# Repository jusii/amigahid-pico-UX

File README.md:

# amigahid-pico

> **Old, moved:** this project is now **Ninepin UX** at [github.com/jusii/ninepin-ux](https://github.com/jusii/ninepin-ux) (boards, firmware, case, full history). This fork stays only for upstream-facing work on [borb/amigahid-pico](https://github.com/borb/amigahid-pico).

**about this fork:** this fork adds support for attaching a *real amiga keyboard* to controller port 2 (build with `-DPORT2_ROLE=KEYBOARD`; see [installation](./doc/installation.md) and [hardware](./doc/hardware.md)). it is based on upstream [pr #44](https://github.com/borb/amigahid-pico/pull/44) (bluetooth support by stefan reinauer) — see that pr for details of the bluetooth work. tested configuration: rev 5 pcb, standard pico (non-w), `BOARD_HIDPICO_REV4` firmware target with `PORT2_ROLE=KEYBOARD`. the original project lives at [borb/amigahid-pico](https://github.com/borb/amigahid-pico).

## introduction

amigahid-pico uses the rp2040 microcontroller (e.g. the raspberry pi pico) in a carrier board to attach usb input devices to a standard amiga without the need for a usb stack on the amiga itself.

it currently supports keyboards and mice and provides connection via the internal keyboard connector, the rj11/din socket on big-box amigas, and via the controller ports.

**this project is very much a work in progress.**

## **important note**

* current kicad files are for the r5 pcb, which is mostly identical to r4. there is no separate r5 firmware target: build `BOARD_HIDPICO_REV4` (the default) — this fork has been built and tested on an r5 board with the rev 4 target. controller port 2 can now be used as an input for a real amiga keyboard via `-DPORT2_ROLE=KEYBOARD` (see the [hardware](./doc/hardware.md) guide for wiring).

* **always read the [errata](./doc/errata.md) section for the current pcb layout before deciding whether or not to build.**

## documentation

* [installation](./doc/installation.md)
* [hardware](./doc/hardware.md)
* [errors in revisions (errata)](./doc/errata.md)

## history

this project is a rewrite of the [amigahid](https://github.com/borb/amigahid) project to the rp2040 microcontroller.

originally, after the retirement of the arduino adk board and shortening availability of the max3421e "usb host shield" for arduino boards, the need for a cheap, easy and continually available replacement was sought.

at first, the uhs mini via a level shifter seemed ideal, but significant issues were found convincing it to work with a variety of arduino boards.

the rp2040 made sense as a target because it is widely available, has sufficient physical connections and is powerful enough to meet multiple needs.

## what is the latency of this?

i have not measured the latency, but the keyboard signals are sent out the moment they are received on the usb bus. the potential latency is likely fractionally longer than the amiga mcu but bear in mind the rp2040 is significantly faster than the standard amiga keyboard controller.

## roadmap

please see the issues tab on the [github repository](https://github.com/borb/amigahid-pico) for the current list of planned features. the tl;dr is:

normal:
* i<sup>2</sup>c display for config/status
* controller emulation
    * keyboard-based controller emulation (use udlr for directions?)
* flash memory-based configuration
* possible amiga-side control panel (using bidirectional controller port signals)
* rotary control simulation (for controlling gotek drives)

crazy talk:
* non-amiga support
* non-hidbp support
* analogue/paddle emulation
* fix some tinyusb issues (hotplug, timing-related instability)

## license

on the fence at the moment, but the current license choice is Eclipse Public License 2.0 (EPL-2.0).

## third party licenses

* µgui: this code contains 'µgui' by achim döbler; the license for this can be read at in the [display readme](./src/display/README.md)

## whuh... who?

nine <[nine@aphlor.org](mailto:nine@aphlor.org)>

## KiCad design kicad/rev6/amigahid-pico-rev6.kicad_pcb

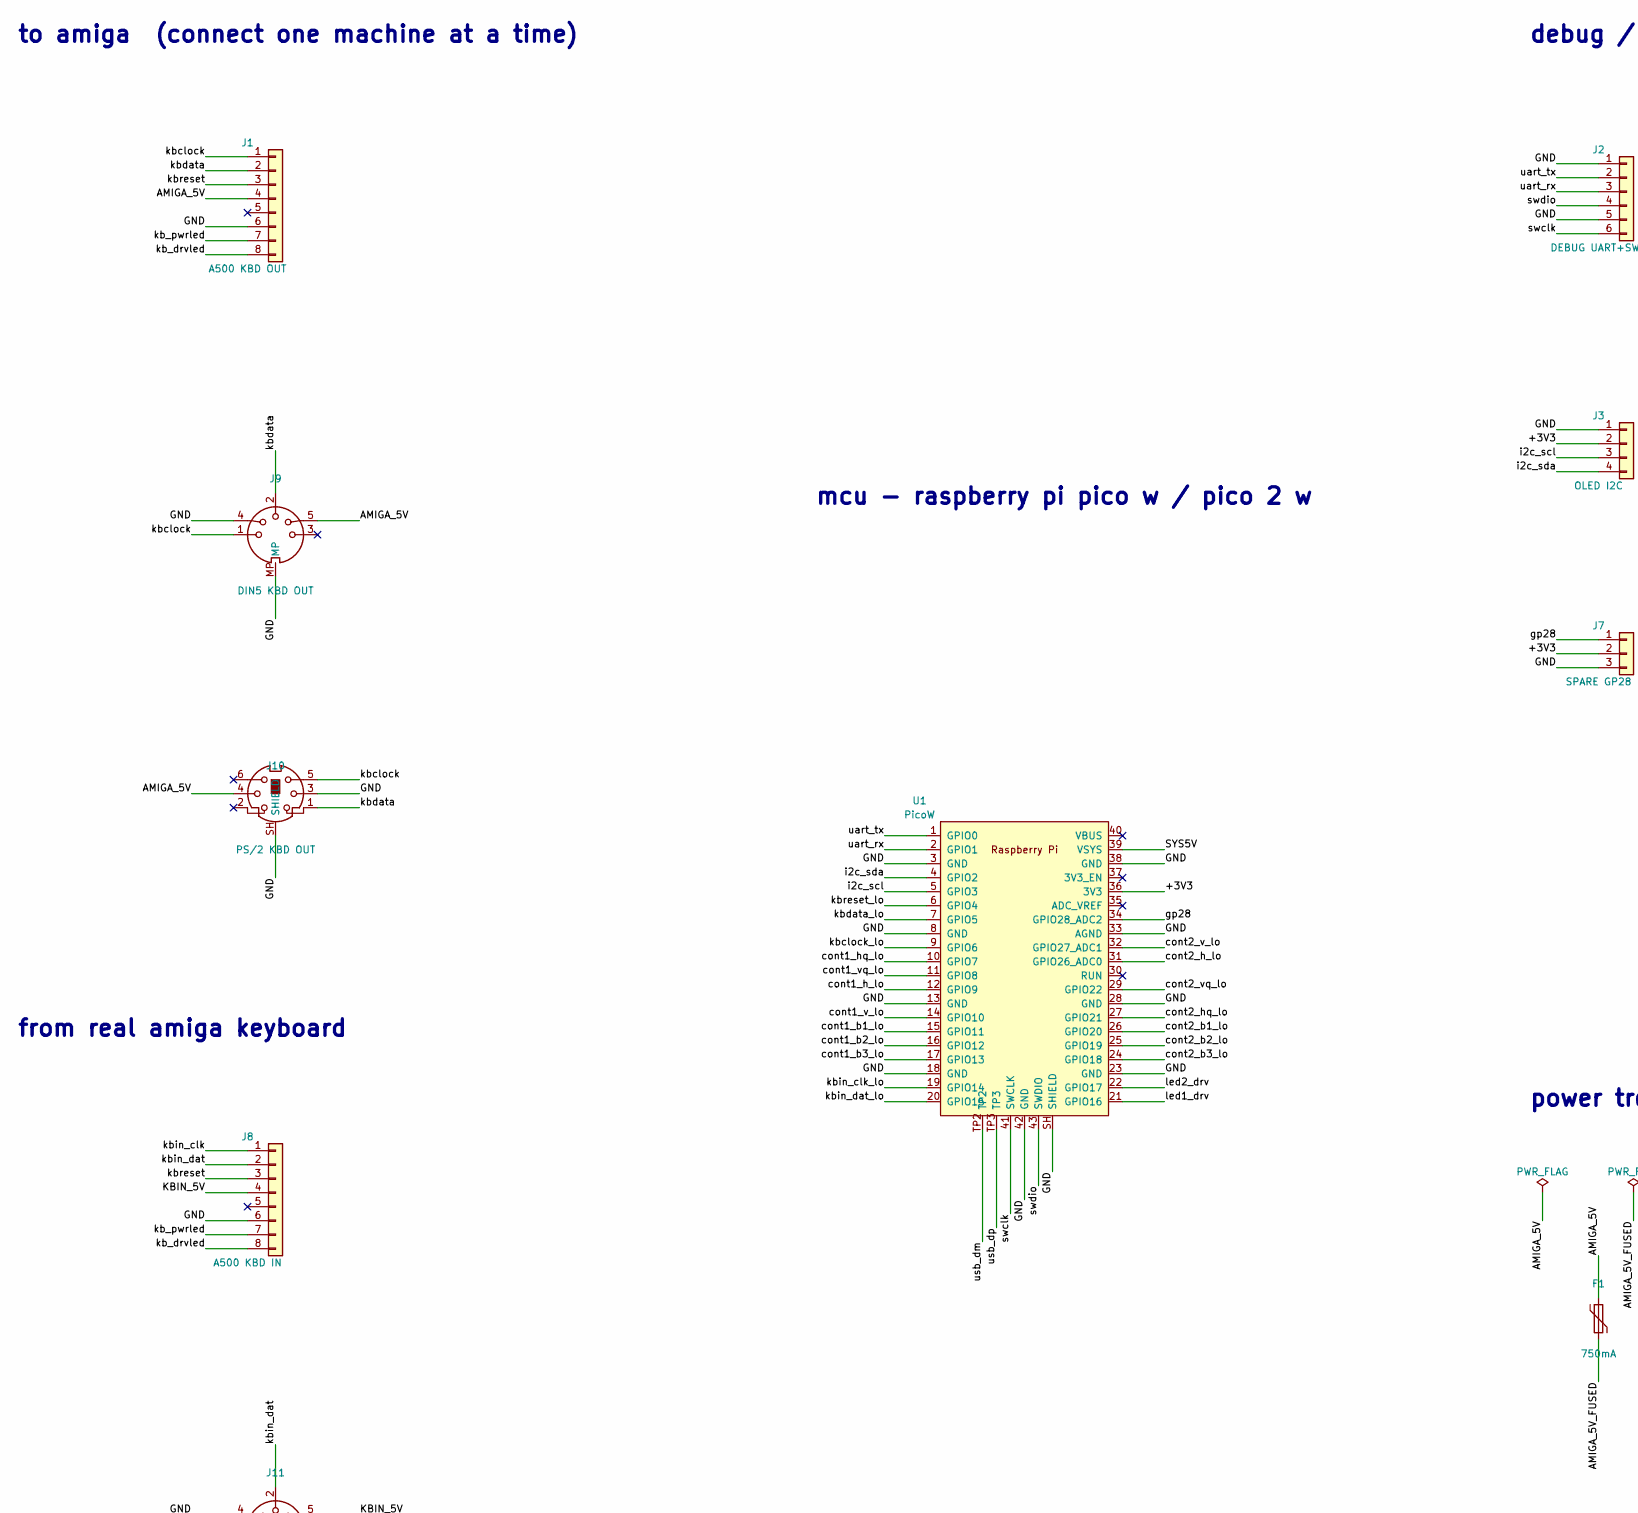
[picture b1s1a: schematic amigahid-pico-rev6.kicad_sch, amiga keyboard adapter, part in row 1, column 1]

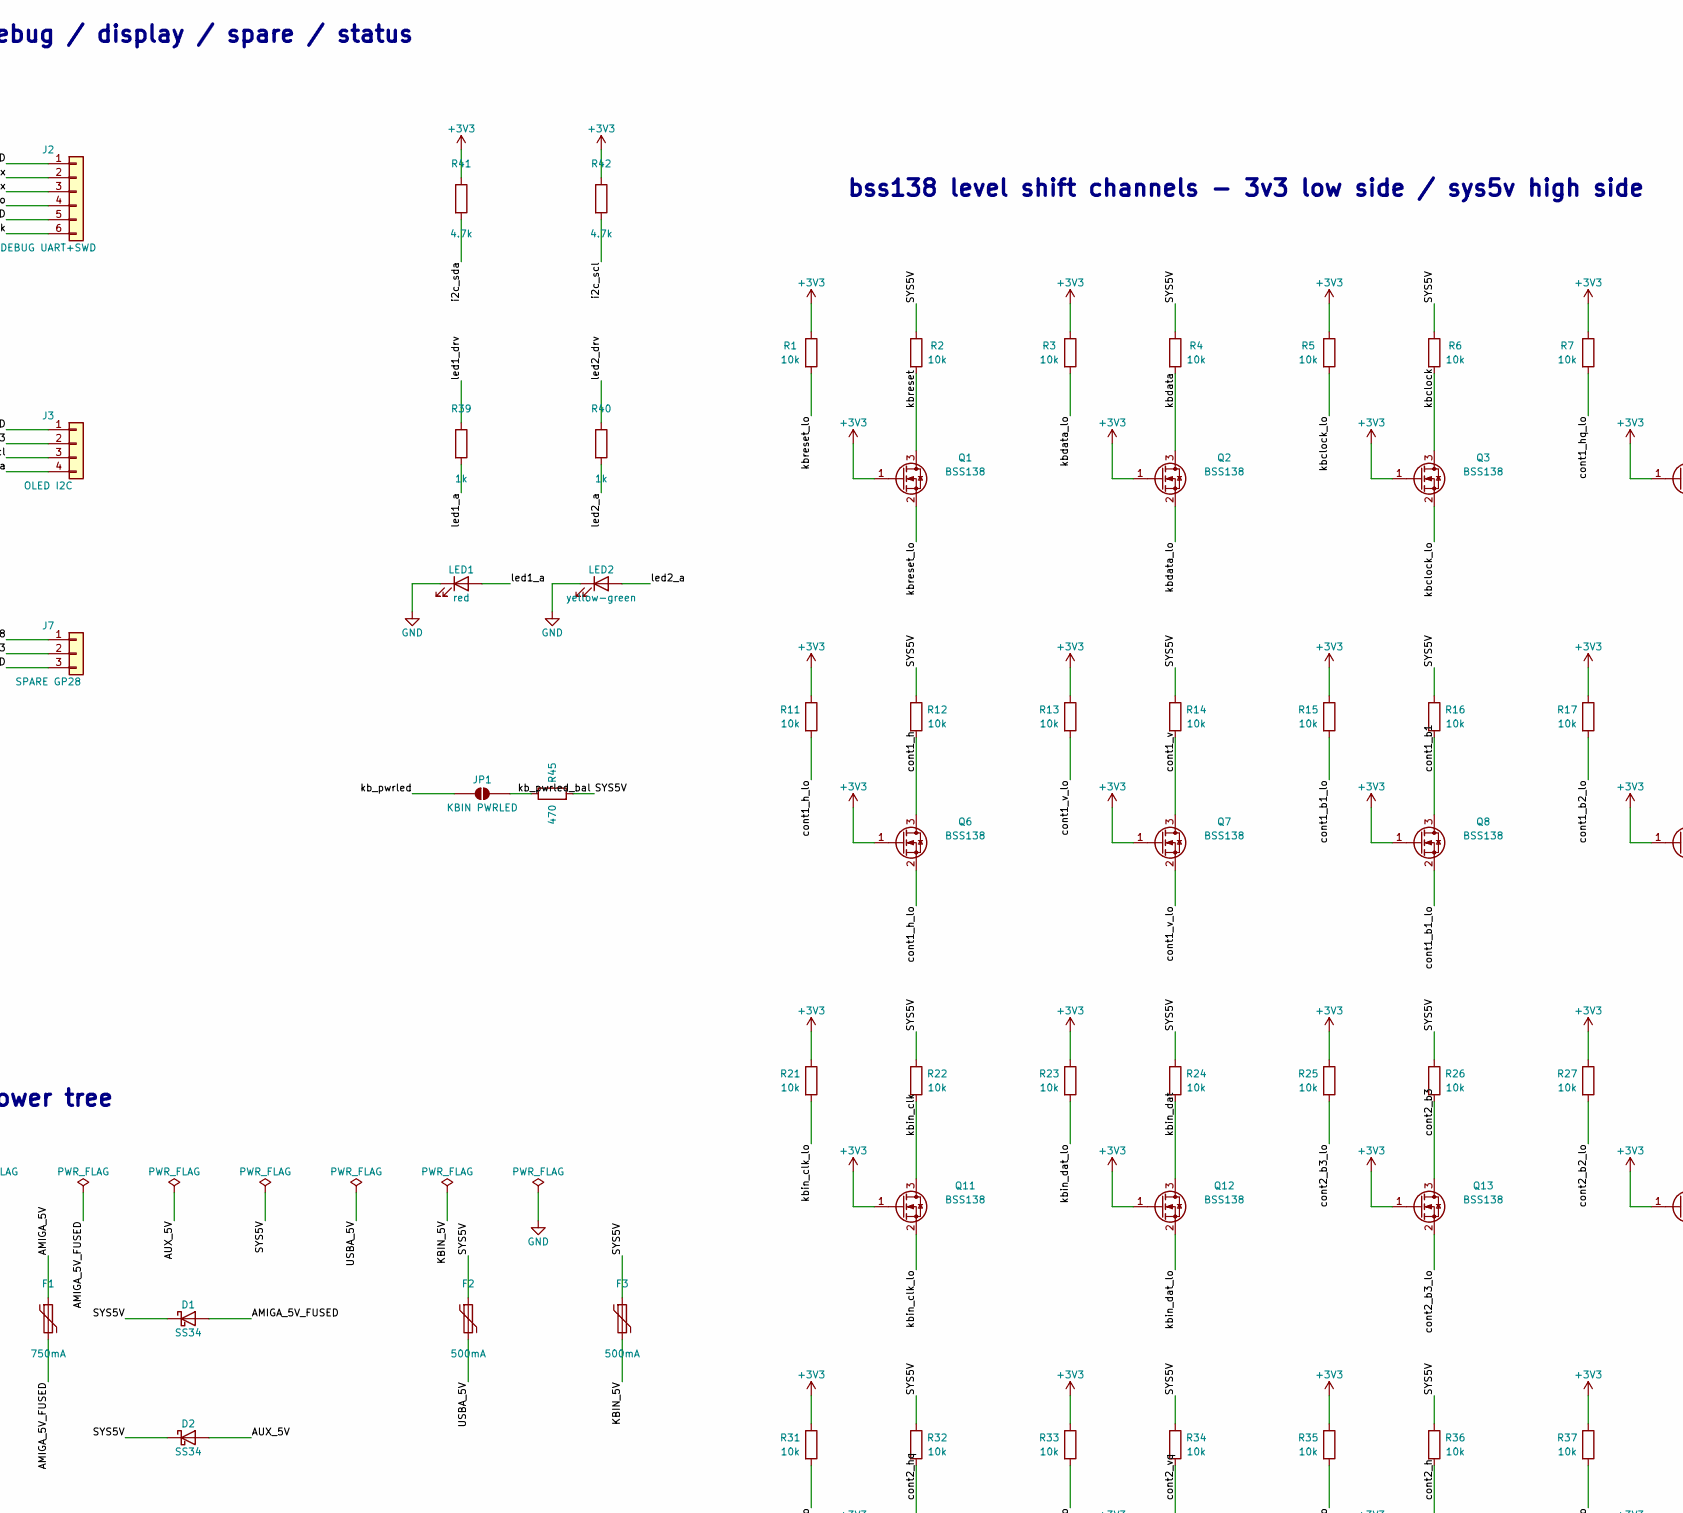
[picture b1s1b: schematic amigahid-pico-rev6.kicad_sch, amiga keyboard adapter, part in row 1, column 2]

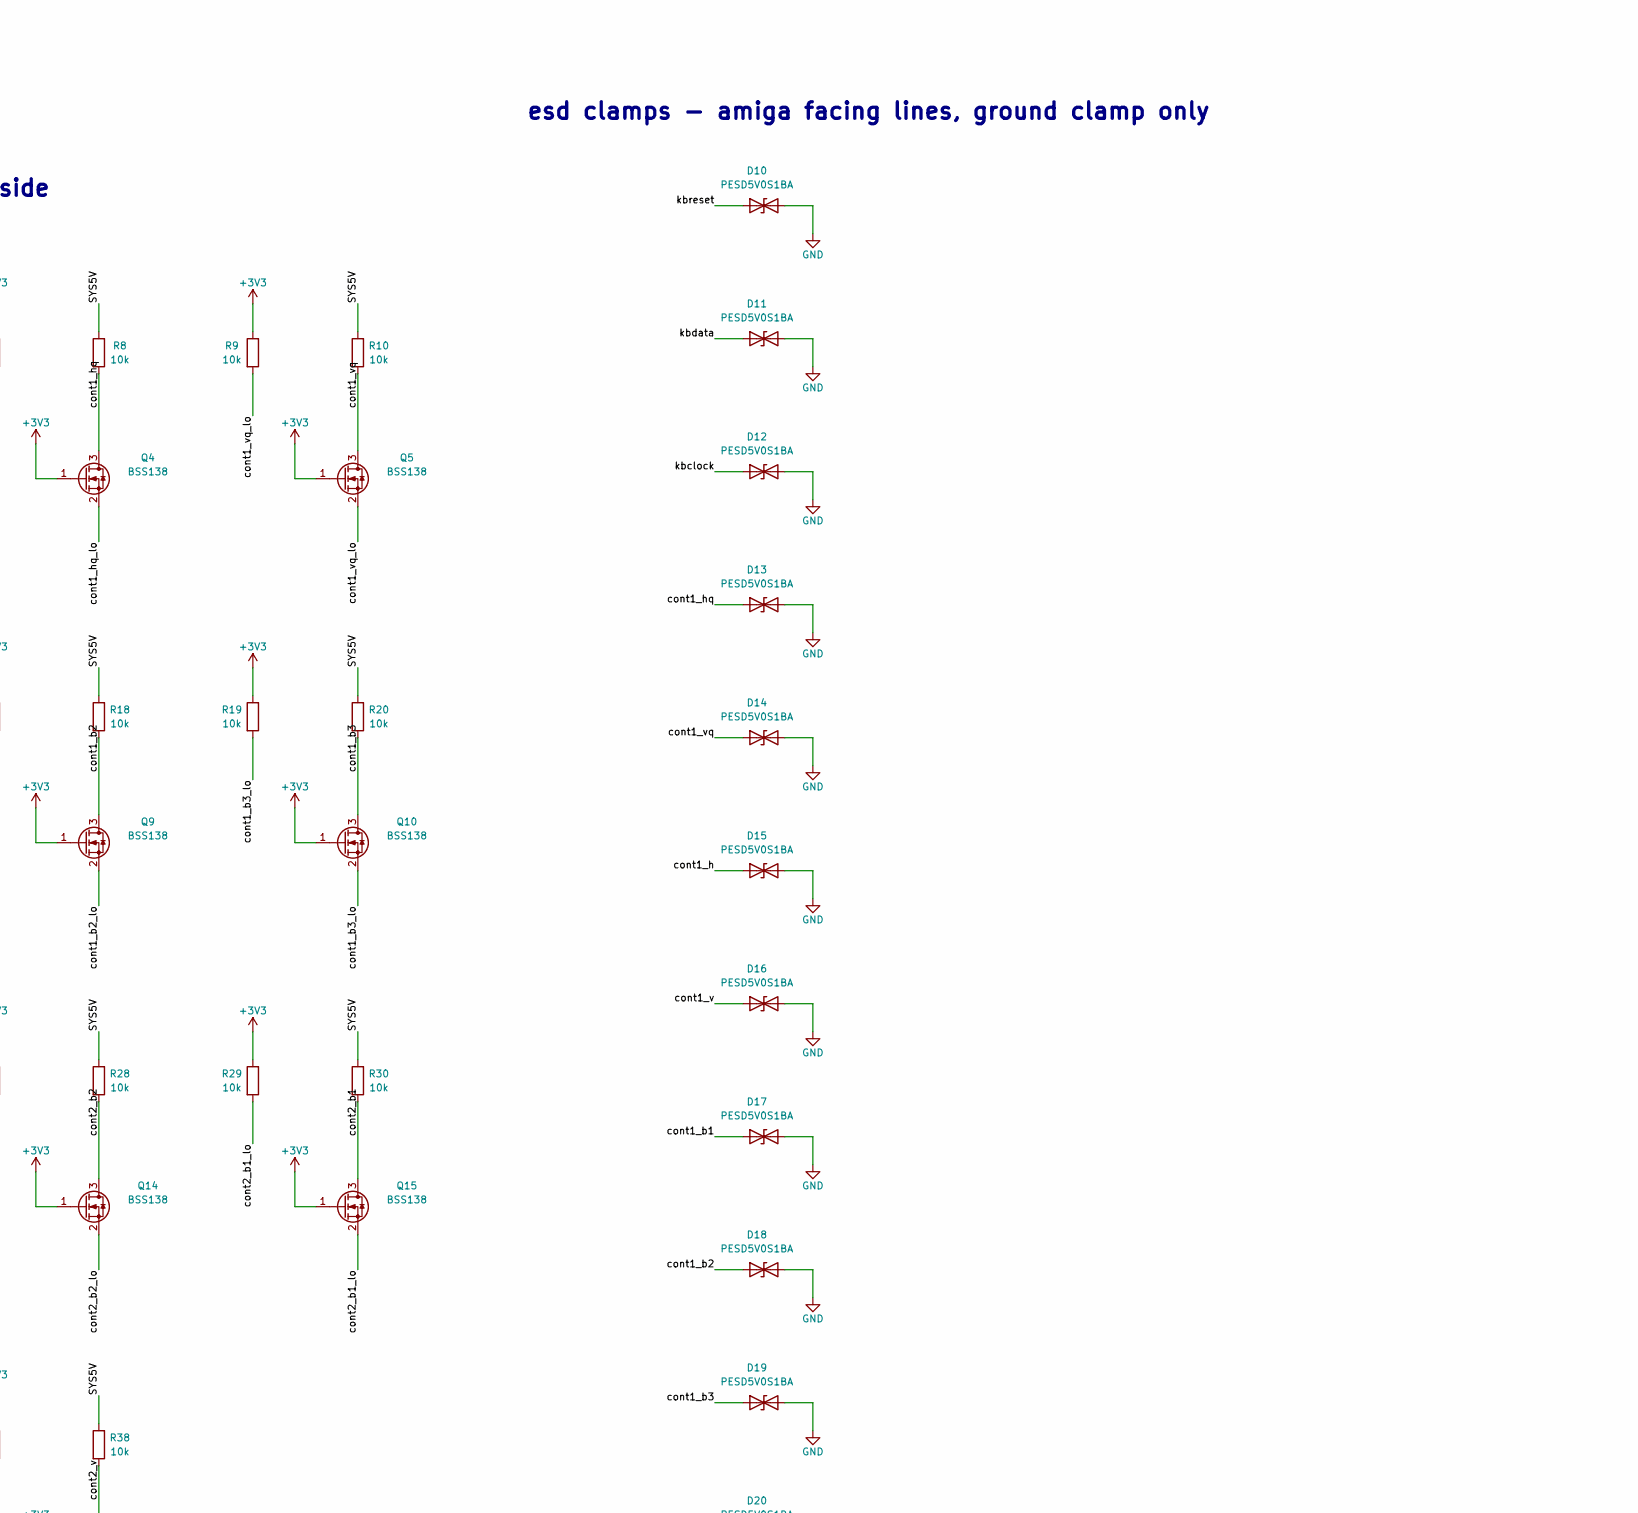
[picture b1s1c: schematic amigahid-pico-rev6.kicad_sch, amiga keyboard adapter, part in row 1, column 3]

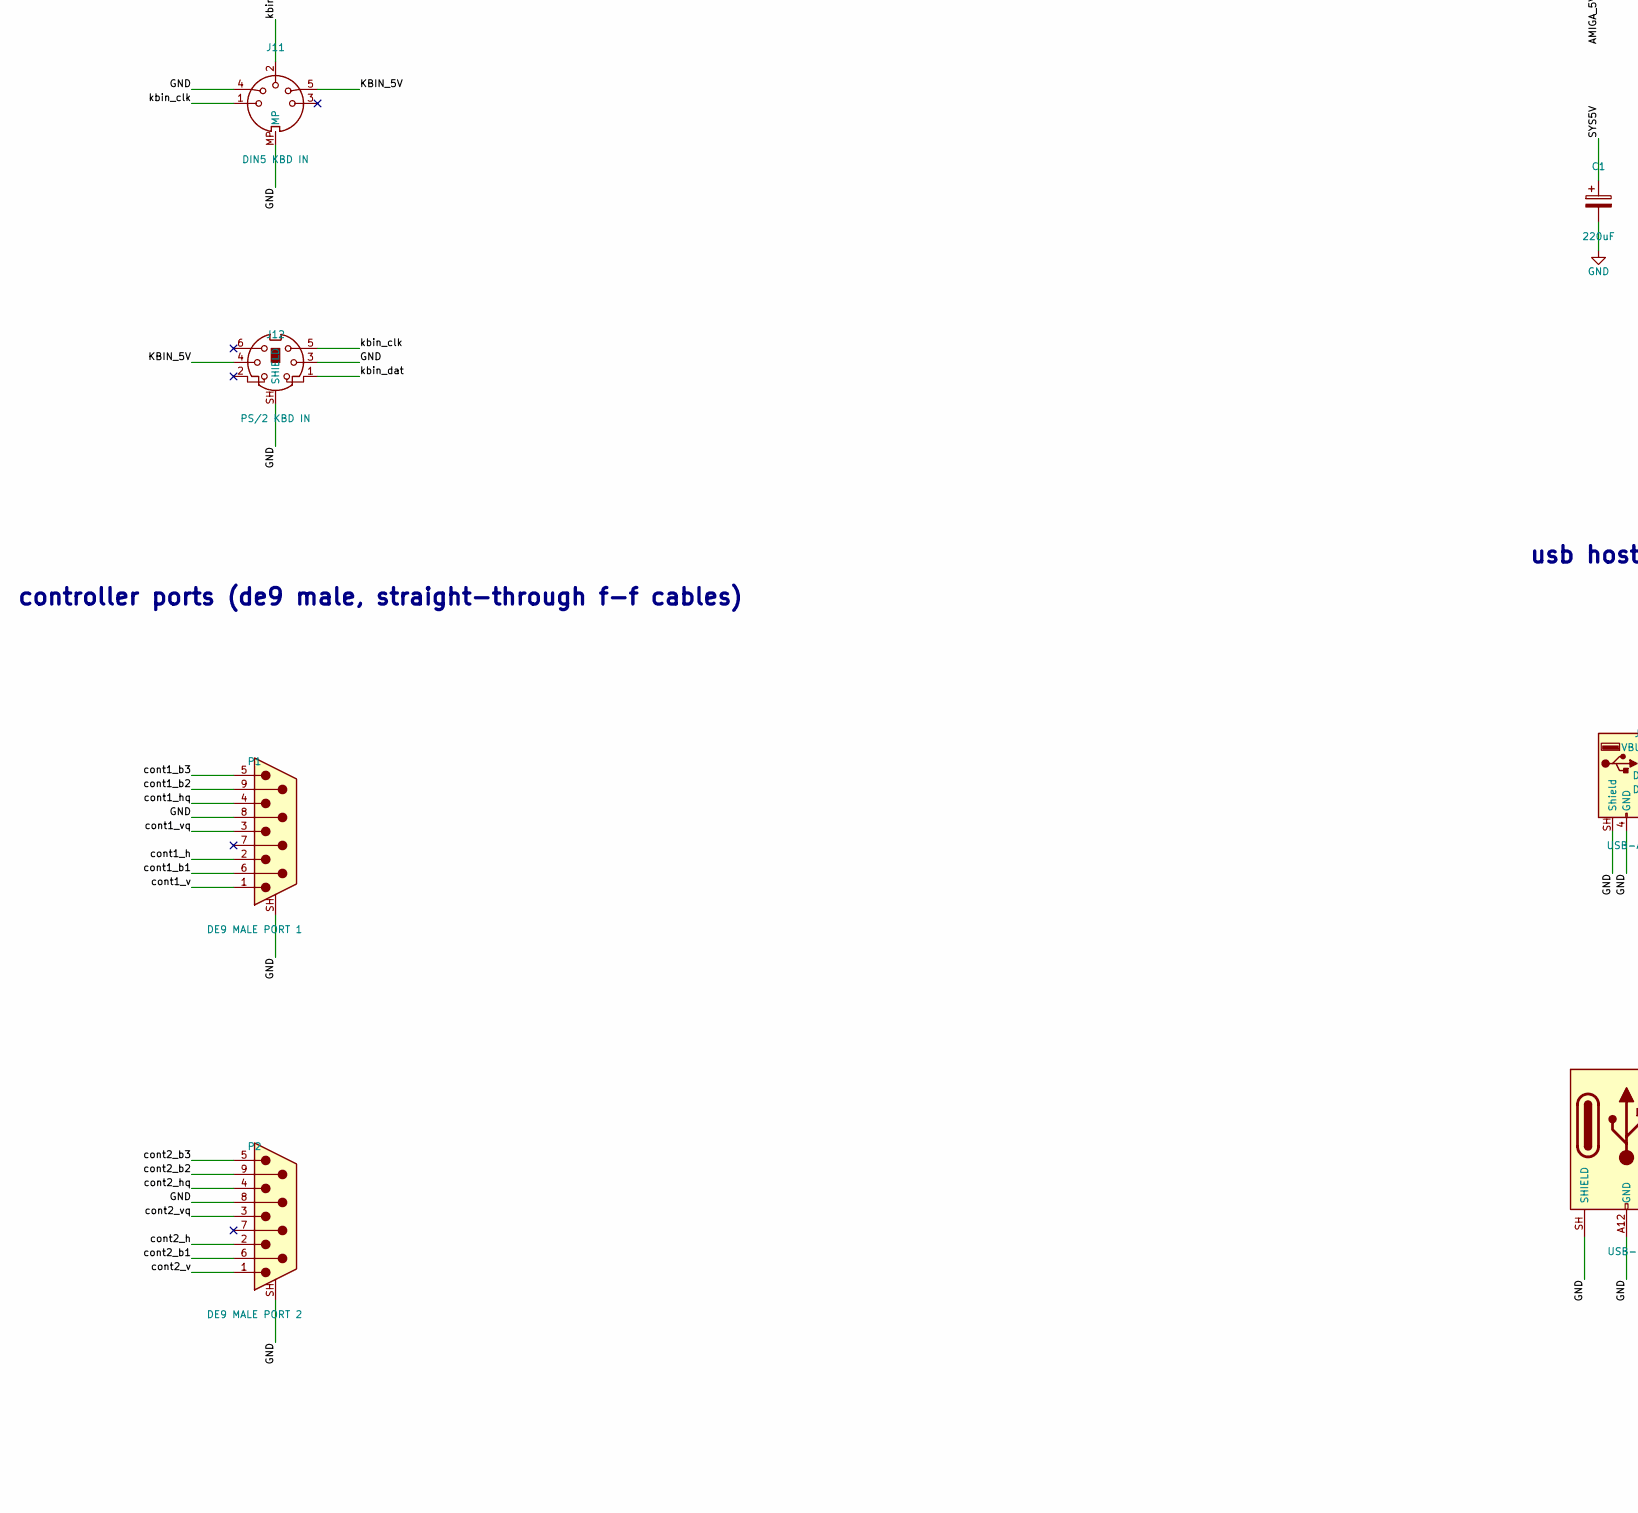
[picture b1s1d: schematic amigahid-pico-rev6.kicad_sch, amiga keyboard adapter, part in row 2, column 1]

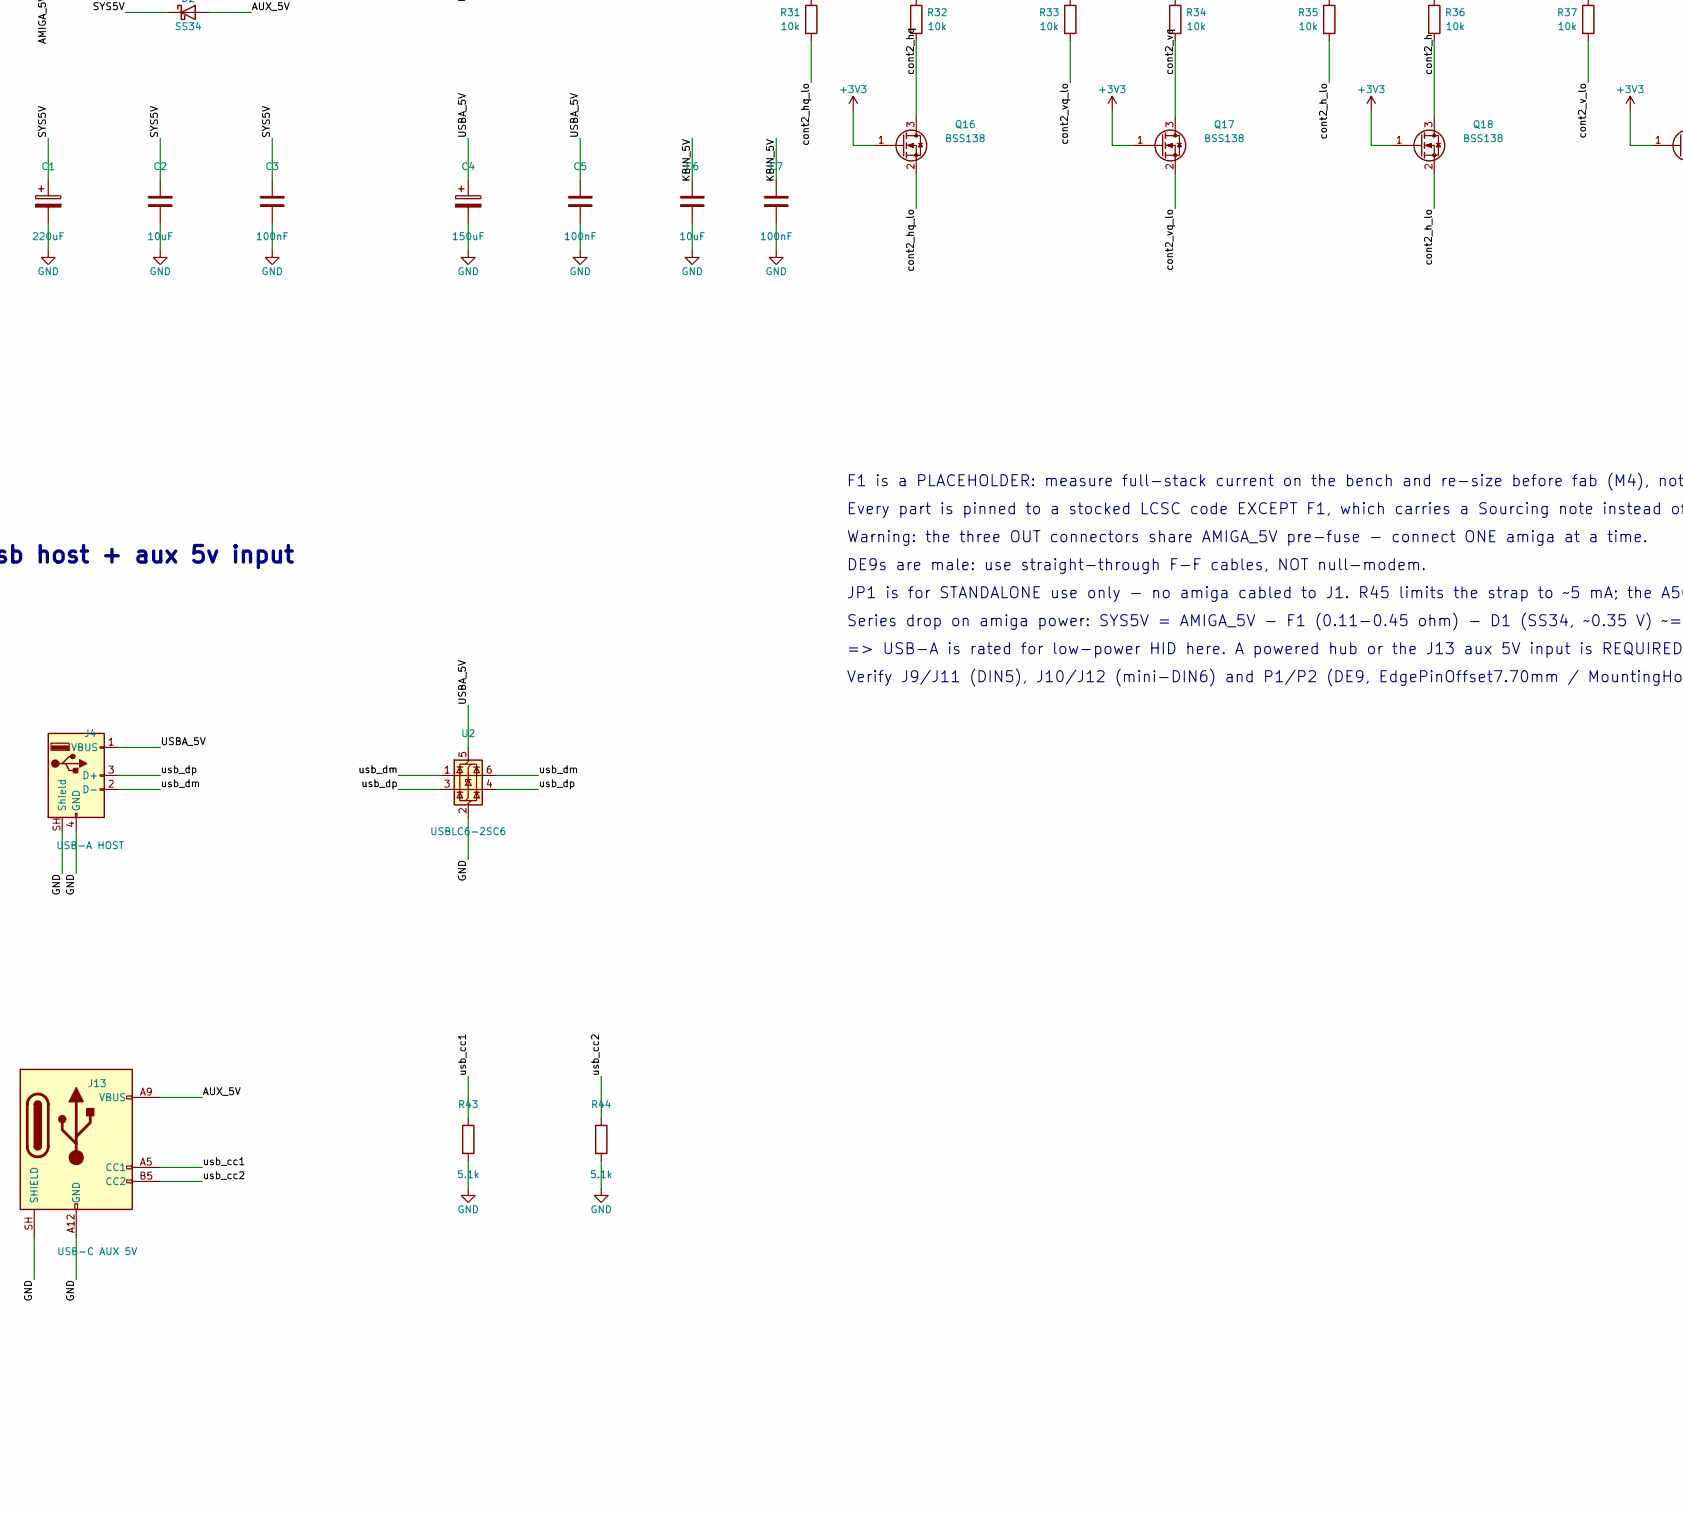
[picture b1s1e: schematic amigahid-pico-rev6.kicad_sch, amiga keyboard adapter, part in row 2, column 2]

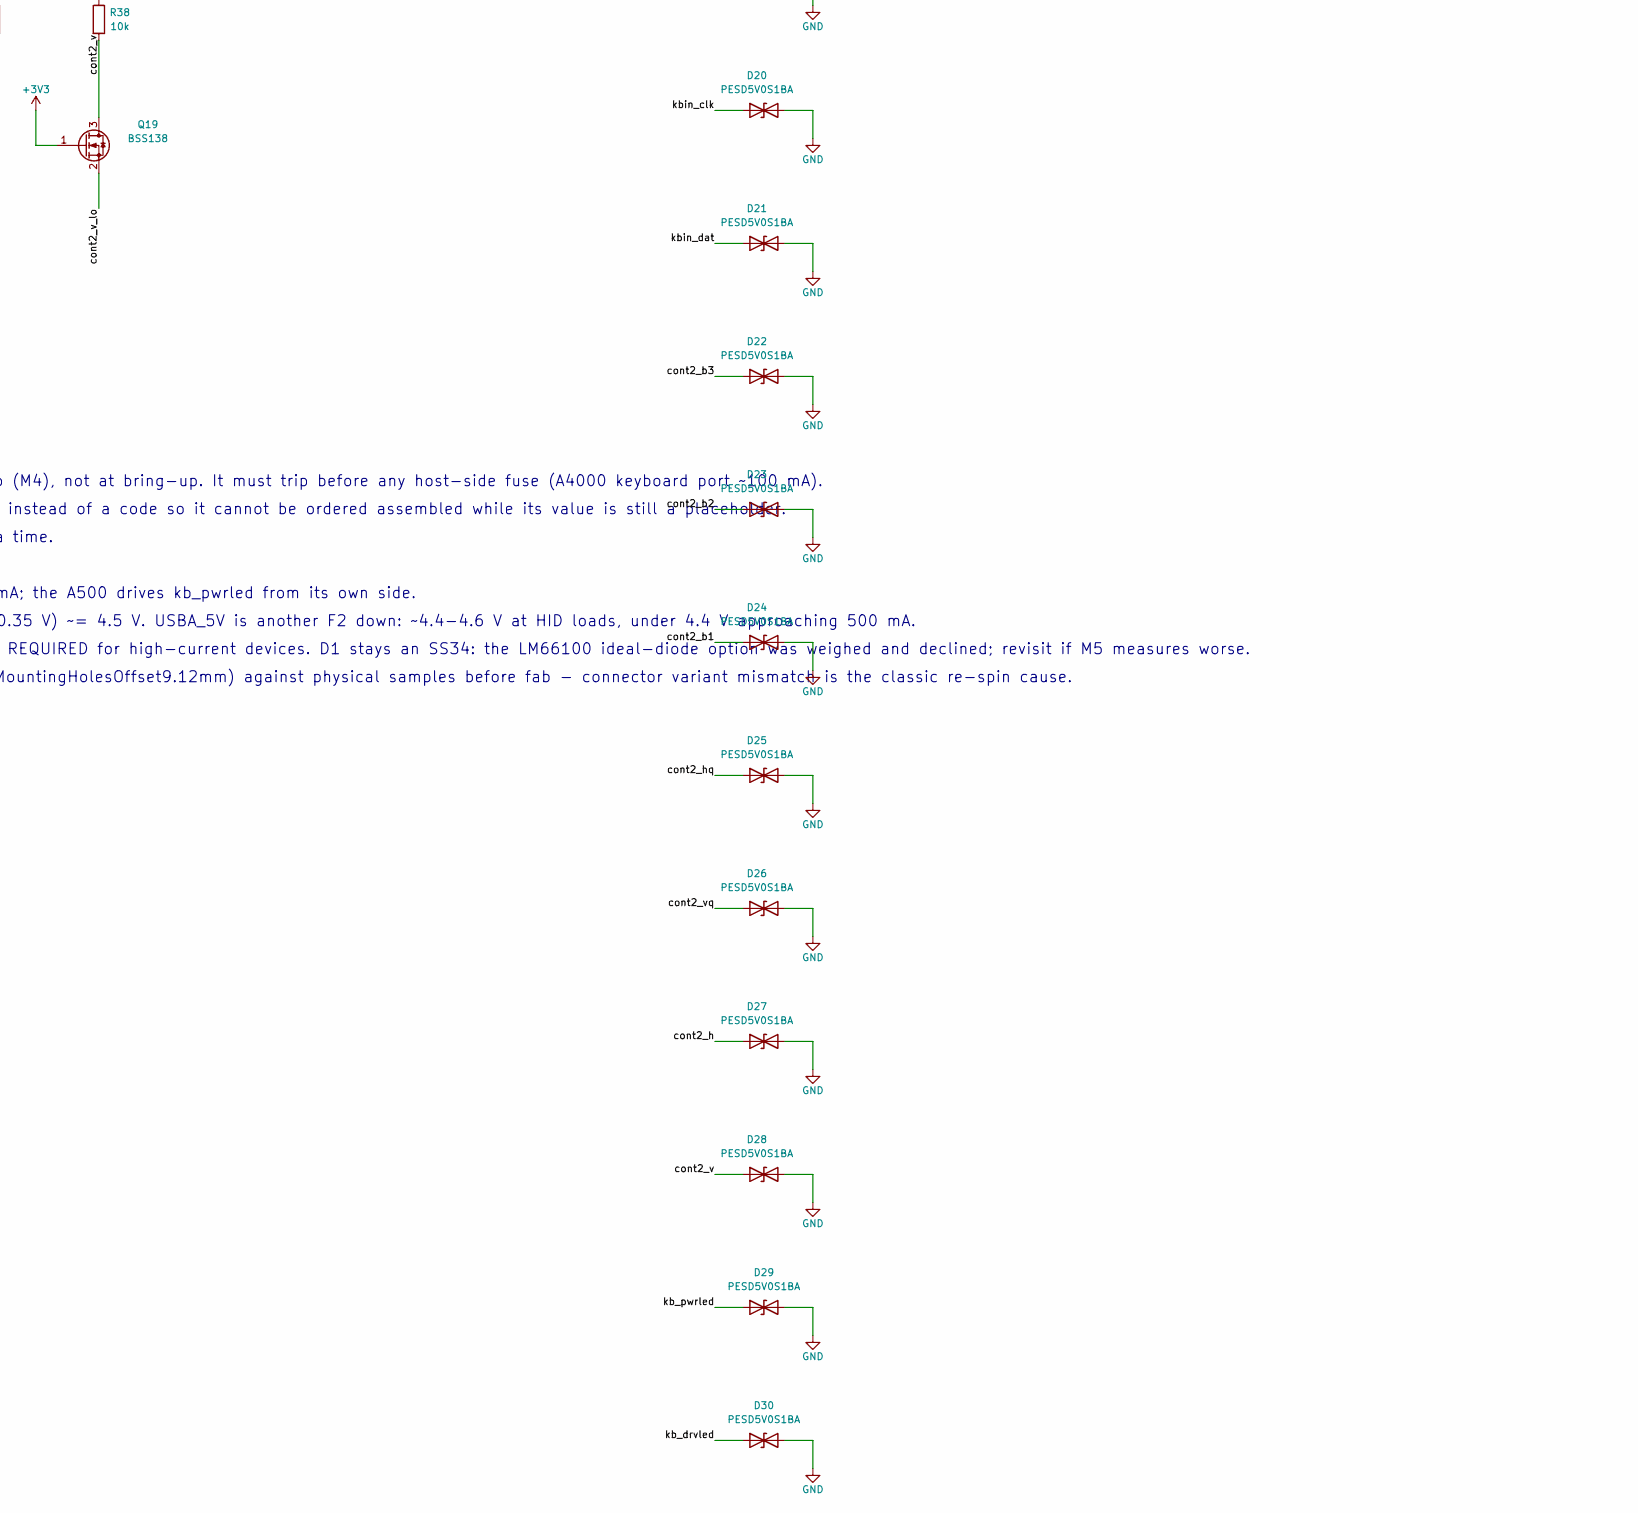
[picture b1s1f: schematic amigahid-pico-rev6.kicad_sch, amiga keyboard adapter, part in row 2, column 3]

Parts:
C1: 220uF; CP_Elec_6.3x7.7; MPN EEE-FK1C221XP; LCSC C128533
C2, C6: 10uF; C_0805_2012Metric; LCSC C15850
C3, C5, C7: 100nF; C_0603_1608Metric; LCSC C14663
C4: 150uF; CP_Elec_6.3x7.7; MPN EEE-FKC151XAP; LCSC C413656
D1, D2: SS34; D_SMA; LCSC C8678
D10, D11, D12, D13, D14, D15, D16, D17, D18, D19, D20, D21, D22, D23, D24, D25, D26, D27, D28, D29, D30: PESD5V0S1BA; D_SOD-323; LCSC C19224
F1: 750mA; Fuse_1812_4532Metric; MPN MF-MSMF075-2
F2, F3: 500mA; Fuse_1812_4532Metric; MPN MF-MSMF050-2; LCSC C17313
J1: A500 KBD OUT; PinHeader_1x08_P2.54mm_Vertical
J2: DEBUG UART+SWD; PinHeader_1x06_P2.54mm_Vertical
J3: OLED I2C; PinSocket_1x04_P2.54mm_Vertical
J4: USB-A HOST; USB_A_Molex_67643_Horizontal
J7: SPARE GP28; PinHeader_1x03_P2.54mm_Vertical
J8: A500 KBD IN; PinHeader_1x08_P2.54mm_Vertical
J9: DIN5 KBD OUT; DIN5_180deg_Socket_Kycon_KCDX-5S-N
J10: PS/2 KBD OUT; MiniDIN6_PS2_Socket_CUI_MD-60S
J11: DIN5 KBD IN; DIN5_180deg_Socket_Kycon_KCDX-5S-N
J12: PS/2 KBD IN; MiniDIN6_PS2_Socket_CUI_MD-60S
J13: USB-C AUX 5V; USB_C_Receptacle_GCT_USB4135-GF-A_6P_TopMnt_Horizontal
JP1: KBIN PWRLED; SolderJumper-2_P1.3mm_Open_RoundedPad1.0x1.5mm
LED1: red; LED_0603_1608Metric; LCSC C2286
LED2: yellow-green; LED_0603_1608Metric; MPN KT-0603YG; LCSC C2289
P1: DE9 MALE PORT 1; DSUB-9_Pins_Horizontal_P2.77x2.84mm_EdgePinOffset7.70mm_Hou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
P2: DE9 MALE PORT 2; DSUB-9_Pins_Horizontal_P2.77x2.84mm_EdgePinOffset7.70mm_Hou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
Q1, Q2, Q3, Q4, Q5, Q6, Q7, Q8, Q9, Q10, Q11, Q12, Q13, Q14, Q15, Q16, Q17, Q18, Q19: BSS138; SOT-23; LCSC C78284
R1, R2, R3, R4, R5, R6, R7, R8, R9, R10, R11, R12, R13, R14, R15, R16, R17, R18, R19, R20, R21, R22, R23, R24, R25, R26, R27, R28, R29, R30, R31, R32, R33, R34, R35, R36, R37, R38: 10k; R_0603_1608Metric; LCSC C25804
R39, R40: 1k; R_0603_1608Metric; LCSC C21190
R41, R42: 4.7k; R_0603_1608Metric; LCSC C23162
R43, R44: 5.1k; R_0603_1608Metric; LCSC C23186
R45: 470; R_0603_1608Metric; LCSC C23179
U1: PicoW; RPi_PicoW_SMD_TH; MPN Raspberry Pi Pico W / Pico 2 W; LCSC n/a (module, hand fitted)
U2: USBLC6-2SC6; SOT-23-6; LCSC C7519

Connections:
+3V3: J3.2, J7.2, Q1.1 (G), Q2.1 (G), Q3.1 (G), Q4.1 (G), Q5.1 (G), Q6.1 (G), Q7.1 (G), Q8.1 (G), Q9.1 (G), Q10.1 (G), Q11.1 (G), Q12.1 (G), Q13.1 (G), Q14.1 (G), Q15.1 (G), Q16.1 (G), Q17.1 (G), Q18.1 (G), Q19.1 (G), R1.1, R3.1, R5.1, R7.1, R9.1, R11.1, R13.1, R15.1, R17.1, R19.1, R21.1, R23.1, R25.1, R27.1, R29.1, R31.1, R33.1, R35.1, R37.1, R41.1, R42.1, U1.36 (3V3)
/AMIGA_5V: F1.1, J1.4, J9.5, J10.4
/AMIGA_5V_FUSED: D1.2 (A), F1.2
/AUX_5V: D2.2 (A), J13.A9 (VBUS), J13.B9 (VBUS)
/KBIN_5V: C6.1, C7.1, F3.2, J8.4, J11.5, J12.4
/SYS5V: C1.1, C2.1, C3.1, D1.1 (K), D2.1 (K), F2.1, F3.1, R2.1, R4.1, R6.1, R8.1, R10.1, R12.1, R14.1, R16.1, R18.1, R20.1, R22.1, R24.1, R26.1, R28.1, R30.1, R32.1, R34.1, R36.1, R38.1, R45.2, U1.39 (VSYS)
/USBA_5V: C4.1, C5.1, F2.2, J4.1 (VBUS), U2.5 (VBUS)
/cont1_b1: D17.1 (A1), P1.6, Q8.3 (D), R16.2
/cont1_b1_lo: Q8.2 (S), R15.2, U1.15 (GPIO11)
/cont1_b2: D18.1 (A1), P1.9, Q9.3 (D), R18.2
/cont1_b2_lo: Q9.2 (S), R17.2, U1.16 (GPIO12)
/cont1_b3: D19.1 (A1), P1.5, Q10.3 (D), R20.2
/cont1_b3_lo: Q10.2 (S), R19.2, U1.17 (GPIO13)
/cont1_h: D15.1 (A1), P1.2, Q6.3 (D), R12.2
/cont1_h_lo: Q6.2 (S), R11.2, U1.12 (GPIO9)
/cont1_hq: D13.1 (A1), P1.4, Q4.3 (D), R8.2
/cont1_hq_lo: Q4.2 (S), R7.2, U1.10 (GPIO7)
/cont1_v: D16.1 (A1), P1.1, Q7.3 (D), R14.2
/cont1_v_lo: Q7.2 (S), R13.2, U1.14 (GPIO10)
/cont1_vq: D14.1 (A1), P1.3, Q5.3 (D), R10.2
/cont1_vq_lo: Q5.2 (S), R9.2, U1.11 (GPIO8)
/cont2_b1: D24.1 (A1), P2.6, Q15.3 (D), R30.2
/cont2_b1_lo: Q15.2 (S), R29.2, U1.26 (GPIO20)
/cont2_b2: D23.1 (A1), P2.9, Q14.3 (D), R28.2
/cont2_b2_lo: Q14.2 (S), R27.2, U1.25 (GPIO19)
/cont2_b3: D22.1 (A1), P2.5, Q13.3 (D), R26.2
/cont2_b3_lo: Q13.2 (S), R25.2, U1.24 (GPIO18)
/cont2_h: D27.1 (A1), P2.2, Q18.3 (D), R36.2
/cont2_h_lo: Q18.2 (S), R35.2, U1.31 (GPIO26_ADC0)
/cont2_hq: D25.1 (A1), P2.4, Q16.3 (D), R32.2
/cont2_hq_lo: Q16.2 (S), R31.2, U1.27 (GPIO21)
/cont2_v: D28.1 (A1), P2.1, Q19.3 (D), R38.2
/cont2_v_lo: Q19.2 (S), R37.2, U1.32 (GPIO27_ADC1)
/cont2_vq: D26.1 (A1), P2.3, Q17.3 (D), R34.2
/cont2_vq_lo: Q17.2 (S), R33.2, U1.29 (GPIO22)
/gp28: J7.1, U1.34 (GPIO28_ADC2)
/i2c_scl: J3.3, R42.2, U1.5 (GPIO3)
/i2c_sda: J3.4, R41.2, U1.4 (GPIO2)
/kb_drvled: D30.1 (A1), J1.8, J8.8
/kb_pwrled: D29.1 (A1), J1.7, J8.7, JP1.1 (A)
/kb_pwrled_bal: JP1.2 (B), R45.1
/kbclock: D12.1 (A1), J1.1, J9.1, J10.5, Q3.3 (D), R6.2
/kbclock_lo: Q3.2 (S), R5.2, U1.9 (GPIO6)
/kbdata: D11.1 (A1), J1.2, J9.2, J10.1, Q2.3 (D), R4.2
/kbdata_lo: Q2.2 (S), R3.2, U1.7 (GPIO5)
/kbin_clk: D20.1 (A1), J8.1, J11.1, J12.5, Q11.3 (D), R22.2
/kbin_clk_lo: Q11.2 (S), R21.2, U1.19 (GPIO14)
/kbin_dat: D21.1 (A1), J8.2, J11.2, J12.1, Q12.3 (D), R24.2
/kbin_dat_lo: Q12.2 (S), R23.2, U1.20 (GPIO15)
/kbreset: D10.1 (A1), J1.3, J8.3, Q1.3 (D), R2.2
/kbreset_lo: Q1.2 (S), R1.2, U1.6 (GPIO4)
/led1_a: LED1.2 (A), R39.2
/led1_drv: R39.1, U1.21 (GPIO16)
/led2_a: LED2.2 (A), R40.2
/led2_drv: R40.1, U1.22 (GPIO17)
/swclk: J2.6, U1.41 (SWCLK)
/swdio: J2.4, U1.43 (SWDIO)
/uart_rx: J2.3, U1.2 (GPIO1)
/uart_tx: J2.2, U1.1 (GPIO0)
/usb_cc1: J13.A5 (CC1), R43.1
/usb_cc2: J13.B5 (CC2), R44.1
/usb_dm: J4.2 (D-), U1.TP2, U2.1 (I/O1), U2.6 (I/O1)
/usb_dp: J4.3 (D+), U1.TP3, U2.3 (I/O2), U2.4 (I/O2)
GND: C1.2, C2.2, C3.2, C4.2, C5.2, C6.2, C7.2, D10.2 (A2), D11.2 (A2), D12.2 (A2), D13.2 (A2), D14.2 (A2), D15.2 (A2), D16.2 (A2), D17.2 (A2), D18.2 (A2), D19.2 (A2), D20.2 (A2), D21.2 (A2), D22.2 (A2), D23.2 (A2), D24.2 (A2), D25.2 (A2), D26.2 (A2), D27.2 (A2), D28.2 (A2), D29.2 (A2), D30.2 (A2), J1.6, J2.1, J2.5, J3.1, J4.4 (GND), J4.SH (Shield), J7.3, J8.6, J9.4, J9.MP, J10.3, J10.SH (SHIELD), J11.4, J11.MP, J12.3, J12.SH (SHIELD), J13.A12 (GND), J13.B12 (GND), J13.SH (SHIELD), LED1.1 (K), LED2.1 (K), P1.8, P1.SH (PAD), P2.8, P2.SH (PAD), R43.2, R44.2, U1.3 (GND), U1.8 (GND), U1.13 (GND), U1.18 (GND), U1.23 (GND), U1.28 (GND), U1.33 (AGND), U1.38 (GND), U1.42 (GND), U1.SH (SHIELD), U2.2 (GND)

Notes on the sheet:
mcu - raspberry pi pico w / pico 2 w
to amiga (connect one machine at a time)
from real amiga keyboard
controller ports (de9 male, straight-through f-f cables)
debug / display / spare / status
power tree
usb host + aux 5v input
bss138 level shift channels - 3v3 low side / sys5v high side
esd clamps - amiga facing lines, ground clamp only
F1 is a PLACEHOLDER: measure full-stack current on the bench and re-size before fab (M4), not at bring-up. It must trip before any host-side fuse (A4000 keyboard port ~100 mA).
Every part is pinned to a stocked LCSC code EXCEPT F1, which carries a Sourcing note instead of a code so it cannot be ordered assembled while its value is still a placeholder.
Warning: the three OUT connectors share AMIGA_5V pre-fuse - connect ONE amiga at a time.
DE9s are male: use straight-through F-F cables, NOT null-modem.
JP1 is for STANDALONE use only - no amiga cabled to J1. R45 limits the strap to ~5 mA; the A500 drives kb_pwrled from its own side.
Series drop on amiga power: SYS5V = AMIGA_5V - F1 (0.11-0.45 ohm) - D1 (SS34, ~0.35 V) ~= 4.5 V. USBA_5V is another F2 down: ~4.4-4.6 V at HID loads, under 4.4 V approaching 500 mA.
=> USB-A is rated for low-power HID here. A powered hub or the J13 aux 5V input is REQUIRED for high-current devices. D1 stays an SS34: the LM66100 ideal-diode option was weighed and declined; revisit if M5 measures worse.
Verify J9/J11 (DIN5), J10/J12 (mini-DIN6) and P1/P2 (DE9, EdgePinOffset7.70mm / MountingHolesOffset9.12mm) against physical samples before fab - connector variant mismatch is the classic re-spin cause.
